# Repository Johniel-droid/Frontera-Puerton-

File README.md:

Perspectiva del proyecto:
**FRONTERA** será desarrollado como un proyecto con enfoque **educativo**,
utilizando un portón automatizado como ejemplo práctico para aprender y aplicar
conceptos de **programación, máquinas de estados, control de motores 
y comunicación Wi-Fi**. El sistema permitirá observar de manera práctica cómo interactúan 
el microcontrolador, sensores, actuadores y comunicación inalámbrica.

El Estudiante tendra el sentir de que esta aplicando inmediatamente lo que aprende.

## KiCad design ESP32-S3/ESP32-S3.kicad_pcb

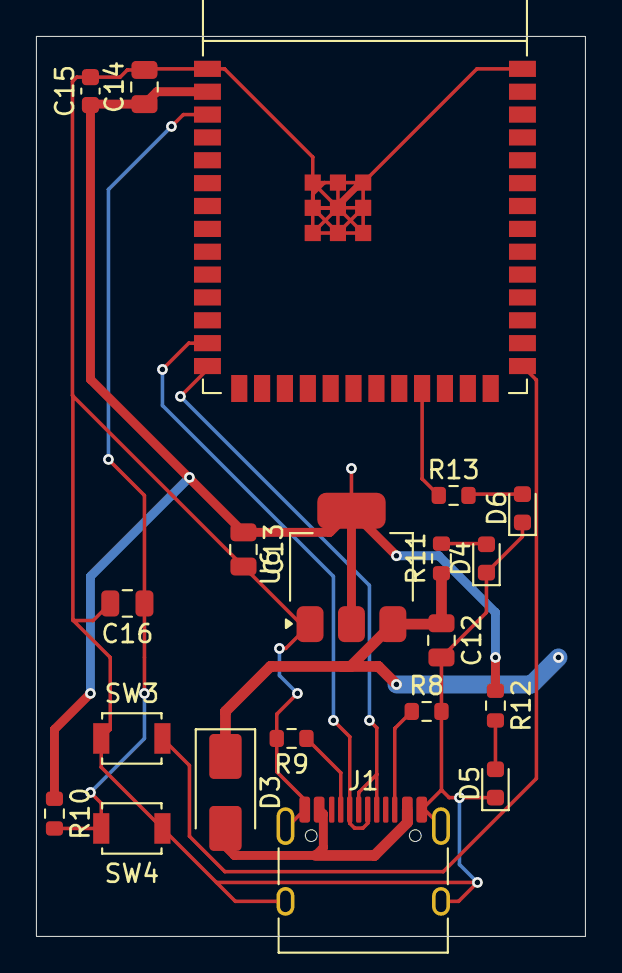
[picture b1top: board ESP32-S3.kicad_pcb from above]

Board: 2 copper layers, 30.5 x 50.0 mm, 20 parts (0 on the bottom side), 14 nets.

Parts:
C12: 10uF; C_0805_2012Metric
C13, C14: 22uF; C_0805_2012Metric
C15: 100nF; C_0603_1608Metric
C16: 10uf; C_0805_2012Metric
D3: D_Schottky; D_SMA
D4: ROJO; LED_0603_1608Metric
D5: VERDE; LED_0603_1608Metric
D6: AZUL; LED_0603_1608Metric
J1: USB_C_Receptacle_USB2.0_16P; USB_C_Receptacle_HRO_TYPE-C-31-M-12
R8: 5.1kΩ; R_0603_1608Metric
R9: 5.1 kΩ; R_0603_1608Metric
R10: 5.1K; R_0603_1608Metric
R11, R12, R13: 5.1k; R_0603_1608Metric
SW3, SW4: SW_SPST; SW_SPST_B3U-1000P
U5: ESP32-S3-WROOM-1
U6: LD1117S33TR_SOT223; SOT-223-3_TabPin2

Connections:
+3V3: C13.1, C14.1, C15.1, R10.1, R12.1, U5.2 (3V3), U6.2 (VO)
+5V: C12.1, D3.1 (K), R11.1, U6.3 (VI)
/D+: J1.A6 (D+), J1.B6 (D+), U5.14 (GPIO20/U1CTS/ADC2_CH9/CLK_OUT1/USB_D+)
/D-: J1.A7 (D-), J1.B7 (D-), U5.13 (GPIO19/U1RTS/ADC2_CH8/CLK_OUT2/USB_D-)
/EN: C16.1, R10.2, SW4.2 (B), U5.3 (EN)
/GPIO0: SW3.2 (B), U5.27 (GPIO0/BOOT)
/GPIO21: R13.1, U5.23 (GPIO21)
GND: C12.2, C13.2, C14.2, C15.2, C16.2, D4.1 (K), D5.1 (K), D6.1 (K), J1.A1 (GND), J1.A12 (GND), J1.B1 (GND), J1.B12 (GND), J1.SH (SHIELD), R8.2, R9.2, SW3.1 (A), SW4.1 (A), U5.1 (GND), U5.40 (GND), U5.41 (GND), U6.1 (GND)
unnamed: D3.2 (A), J1.A4 (VBUS), J1.A9 (VBUS), J1.B4 (VBUS), J1.B9 (VBUS)
unnamed: D4.2 (A), R11.2
unnamed: D5.2 (A), R12.2
unnamed: D6.2 (A), R13.2
unnamed: J1.A5 (CC1), R9.1
unnamed: J1.B5 (CC2), R8.1

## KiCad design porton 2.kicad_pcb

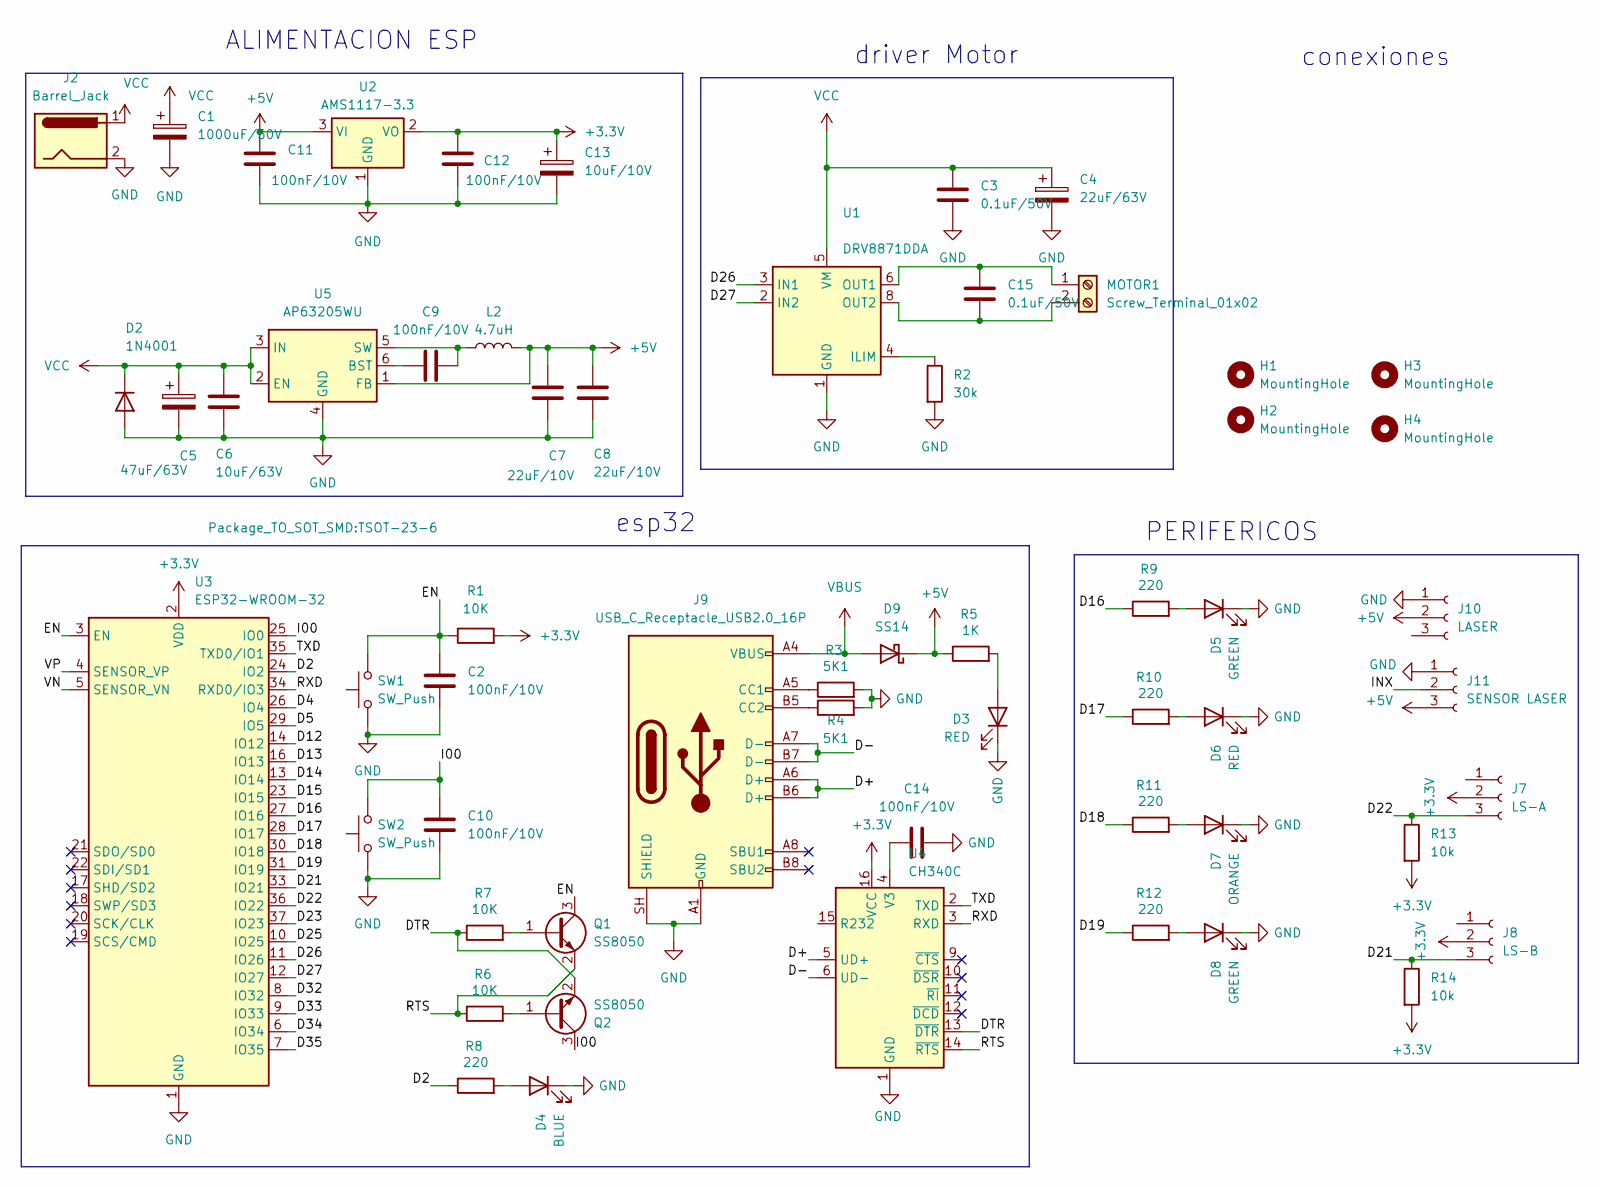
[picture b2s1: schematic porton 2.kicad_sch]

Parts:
C1: 1000uF/50V; CP_Elec_6.3x7.7
C2, C9, C10, C11, C12, C14: 100nF/10V; C_0805_2012Metric
C3, C15: 0.1uF/50V; C_0805_2012Metric
C4: 22uF/63V; CP_Elec_6.3x7.7
C5: 47uF/63V; CP_Elec_6.3x7.7
C6: 10uF/63V; C_0805_2012Metric
C7, C8: 22uF/10V; C_0805_2012Metric
C13: 10uF/10V; CP_EIA-3528-21_Kemet-B_HandSolder
D2: 1N4001; D_SMA_Handsoldering
D3, D6: RED; LED_1206_3216Metric
D4: BLUE; LED_1206_3216Metric
D5, D8: GREEN; LED_1206_3216Metric
D7: ORANGE; LED_1206_3216Metric
D9: SS14; D_SMA
H1, H2, H3, H4: MountingHole; MountingHole_2.5mm
J2: Barrel_Jack; BarrelJack_GCT_DCJ200-10-A_Horizontal
J7: LS-A; JST_PH_B3B-PH-K_1x03_P2.00mm_Vertical
J8: LS-B; JST_PH_B3B-PH-K_1x03_P2.00mm_Vertical
J9: USB_C_Receptacle_USB2.0_16P; USB_C_Receptacle_Amphenol_12401948E412A
J10: LASER; JST_PH_B3B-PH-K_1x03_P2.00mm_Vertical
J11: SENSOR LASER; JST_PH_B3B-PH-K_1x03_P2.00mm_Vertical
L2: 4.7uH; L_Chilisin_BMRB00050518-B
MOTOR1: Screw_Terminal_01x02; TerminalBlock_MaiXu_MX126-5.0-02P_1x02_P5.00mm
Q1, Q2: SS8050; SOT-23
R1, R6, R7: 10K; R_0805_2012Metric_Pad1.20x1.40mm_HandSolder
R2: 30k; R_0805_2012Metric_Pad1.20x1.40mm_HandSolder
R3, R4: 5K1; R_0805_2012Metric_Pad1.20x1.40mm_HandSolder
R5: 1K; R_0805_2012Metric_Pad1.20x1.40mm_HandSolder
R8, R9, R10, R11, R12: 220; R_0805_2012Metric_Pad1.20x1.40mm_HandSolder
R13, R14: 10k; R_0805_2012Metric_Pad1.20x1.40mm_HandSolder
SW1, SW2: SW_Push; SW_Tactile_SPST_NO_Straight_CK_PTS636Sx25SMTRLFS
U1: DRV8871DDA; Texas_HTSOP-8-1EP_3.9x4.9mm_P1.27mm_EP2.95x4.9mm_Mask2.4x3.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
U2: AMS1117-3.3; SOT-223-3_TabPin2; lcsc C6186
U3: ESP32-WROOM-32; lcsc C701341
U4: CH340C; SOIC-16_3.9x9.9mm_P1.27mm
U5: AP63205WU; TSOT-23-6

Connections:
+3.3V: C12.2, C13.1, J7.2, J8.2, R1.2, R13.2, R14.2, U2.2 (VO), U3.2 (VDD), U4.16 (VCC)
+5V: C7.1, C8.1, C11.2, D9.1 (K), J10.2, J11.3, L2.2, R5.1, U2.3 (VI), U5.1 (FB)
/D2: R8.1, U3.24 (IO2)
/D4: U3.26 (IO4)
/D5: U3.29 (IO5)
/D12: U3.14 (IO12)
/D13: U3.16 (IO13)
/D14: U3.13 (IO14)
/D15: U3.23 (IO15)
/D16: R9.1, U3.27 (IO16)
/D17: R10.1, U3.28 (IO17)
/D18: R11.1, U3.30 (IO18)
/D19: R12.1, U3.31 (IO19)
/D21: J8.3, R14.1, U3.33 (IO21)
/D22: J7.3, R13.1, U3.36 (IO22)
/D23: U3.37 (IO23)
/D25: U3.10 (IO25)
/D26: U1.3 (IN1), U3.11 (IO26)
/D27: U1.2 (IN2), U3.12 (IO27)
/D32: U3.8 (IO32)
/D33: U3.9 (IO33)
/D34: U3.6 (IO34)
/D35: U3.7 (IO35)
/D+: J9.A6 (D+), J9.B6 (D+), U4.5 (UD+)
/D-: J9.A7 (D-), J9.B7 (D-), U4.6 (UD-)
/DTR: Q2.2 (E), R7.1, U4.13 (~DTR)
/EN: C2.2, Q1.3 (C), R1.1, SW1.2, U3.3 (EN)
/I00: C10.2, Q2.3 (C), SW2.2, U3.25 (IO0)
/INX: J11.2
/RTS: Q1.2 (E), R6.1, U4.14 (~RTS)
/RXD: U3.34 (RXD0/IO3), U4.3 (RXD)
/TXD: U3.35 (TXD0/IO1), U4.2 (TXD)
/VN: U3.5 (SENSOR_VN)
/VP: U3.4 (SENSOR_VP)
GND: C1.2, C2.1, C3.2, C4.2, C5.2, C6.2, C7.2, C8.2, C10.1, C11.1, C12.1, C13.2, C14.1, D2.2 (A), D3.1 (K), D4.1 (K), D5.1 (K), D6.1 (K), D7.1 (K), D8.1 (K), J2.2, J9.A1 (GND), J9.A12 (GND), J9.B1 (GND), J9.B12 (GND), J9.SH (SHIELD), J10.1, J11.1, R2.2, R3.2, R4.2, SW1.1, SW2.1, U1.1 (GND), U1.7 (GND), U1.9 (GND), U2.1 (GND), U3.1 (GND), U3.15 (GND), U3.38 (GND), U3.39 (GND), U4.1 (GND), U5.4 (GND)
unnamed: D3.2 (A), R5.2
unnamed: D4.2 (A), R8.2
unnamed: D5.2 (A), R9.2
unnamed: D6.2 (A), R10.2
unnamed: D7.2 (A), R11.2
unnamed: D8.2 (A), R12.2
unnamed: J9.A5 (CC1), R3.1
unnamed: J9.B5 (CC2), R4.1
unnamed: C15.1, MOTOR1.1, U1.6 (OUT1)
unnamed: C15.2, MOTOR1.2, U1.8 (OUT2)
unnamed: Q1.1 (B), R7.2
unnamed: Q2.1 (B), R6.2
unnamed: R2.1, U1.4 (ILIM)
unnamed: C14.2, U4.4 (V3)
unnamed: C9.1, U5.6 (BST)
unnamed: C9.2, L2.1, U5.5 (SW)
VBUS: D9.2 (A), J9.A4 (VBUS), J9.A9 (VBUS), J9.B4 (VBUS), J9.B9 (VBUS)
VCC: C1.1, C3.1, C4.1, C5.1, C6.1, D2.1 (K), J2.1, U1.5 (VM), U5.2 (EN), U5.3 (IN)

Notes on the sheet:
ALIMENTACION ESP
driver Motor
PERIFERICOS
conexiones
esp32

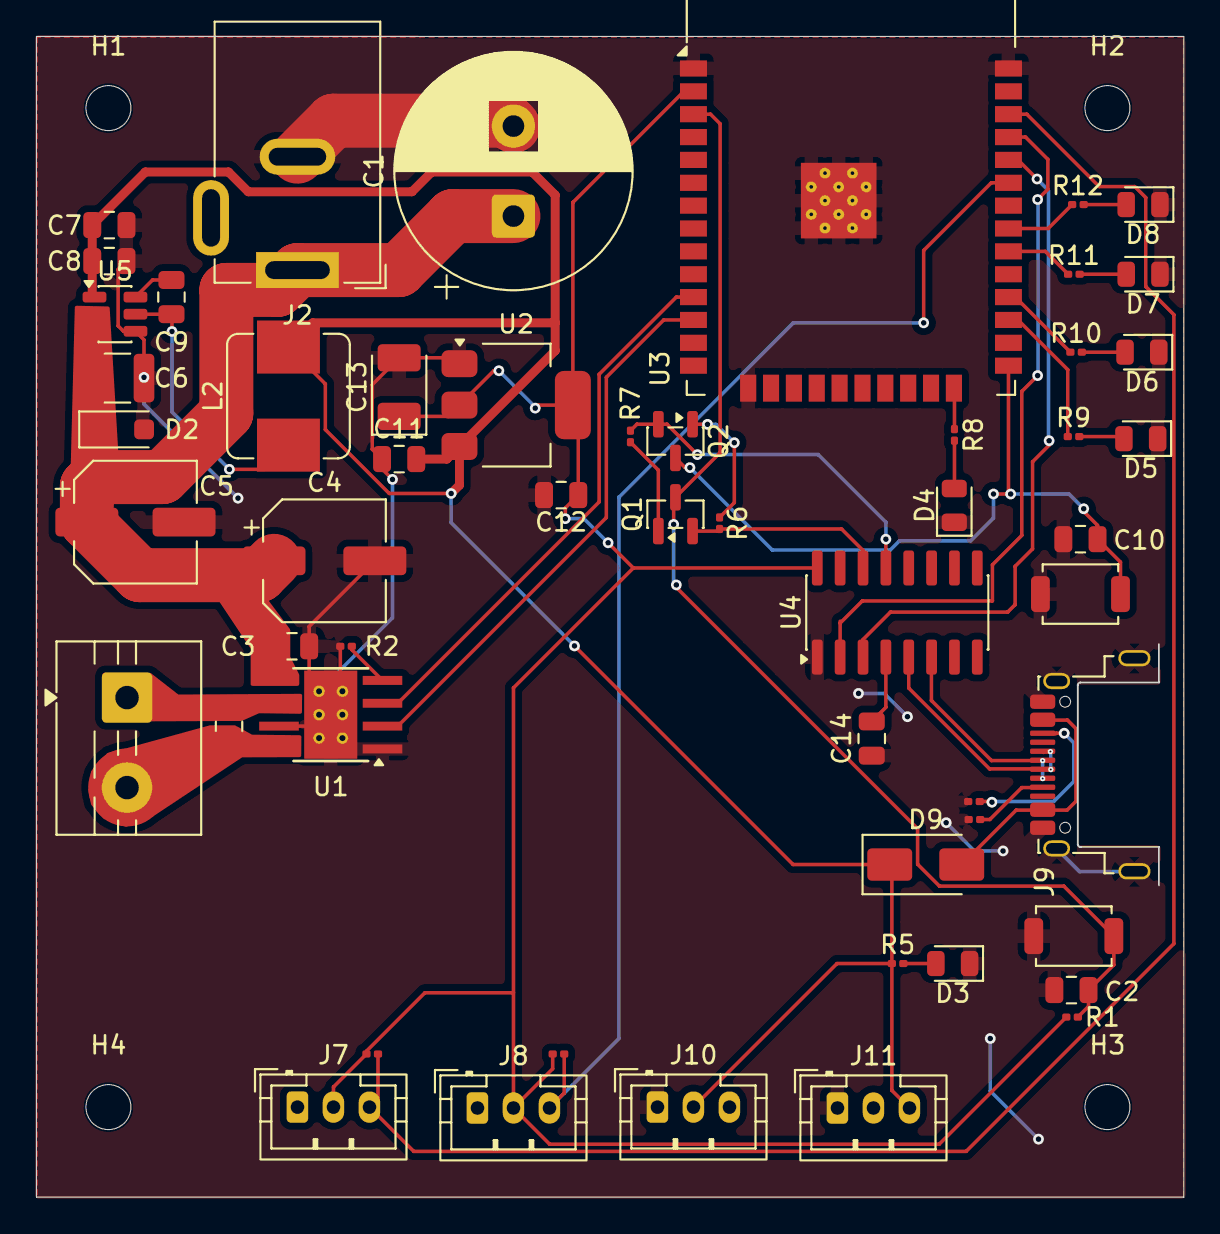
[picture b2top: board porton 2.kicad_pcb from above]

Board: 2 copper layers, 63.7 x 64.5 mm, 58 parts (0 on the bottom side), 38 nets.
